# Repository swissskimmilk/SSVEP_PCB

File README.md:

# SSVEP EEG board

A 4-channel EEG board that streams over BLE, with a photodiode that marks screen flashes
in the same samples as the EEG.

```
host/      PyQt6 control + stimulus windows, recording, analysis
firmware/  XIAO nRF52840 firmware (PlatformIO)
SSVEP_PCB/ KiCad project
design/    circuit JSON, BOM, scripts
fab/       Gerbers
```

## Quick start

```
cd host && pip install -e . && python -m ssvep_host    # pick "Simulator" to try it
cd firmware && pio run -t upload                        # flash the board over USB
```

## Docs

- [Running a session](docs/session.md)
- [Hardware](docs/hardware.md)
- [Protocol](docs/protocol.md)
- [Bring-up](docs/bringup.md)

> Never put electrodes on a person while USB is plugged in. Battery and BLE only.

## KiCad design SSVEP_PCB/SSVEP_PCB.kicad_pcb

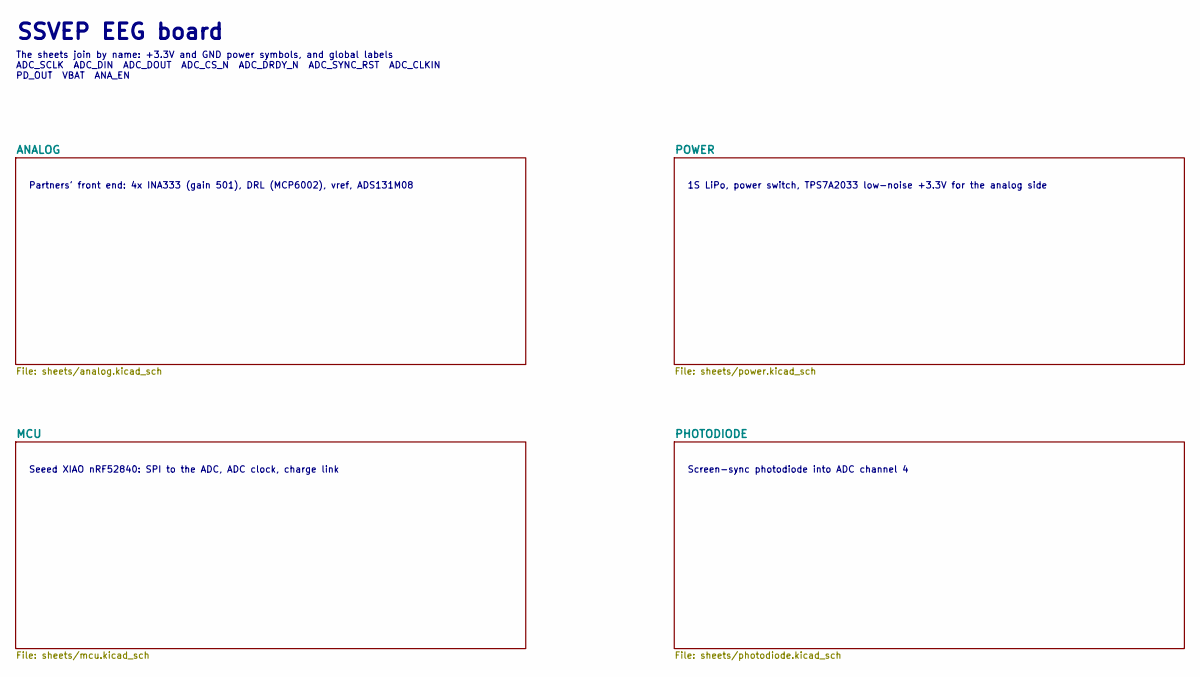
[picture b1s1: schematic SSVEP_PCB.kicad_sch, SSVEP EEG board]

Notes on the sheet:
SSVEP EEG board
The sheets join by name: +3.3V and GND power symbols, and global labels ADC_SCLK ADC_DIN ADC_DOUT ADC_CS_N ADC_DRDY_N ADC_SYNC_RST ADC_CLKIN PD_OUT VBAT ANA_EN
Partners' front end: 4x INA333 (gain 501), DRL (MCP6002), vref, ADS131M08
1S LiPo, power switch, TPS7A2033 low-noise +3.3V for the analog side
Seeed XIAO nRF52840: SPI to the ADC, ADC clock, charge link
Screen-sync photodiode into ADC channel 4

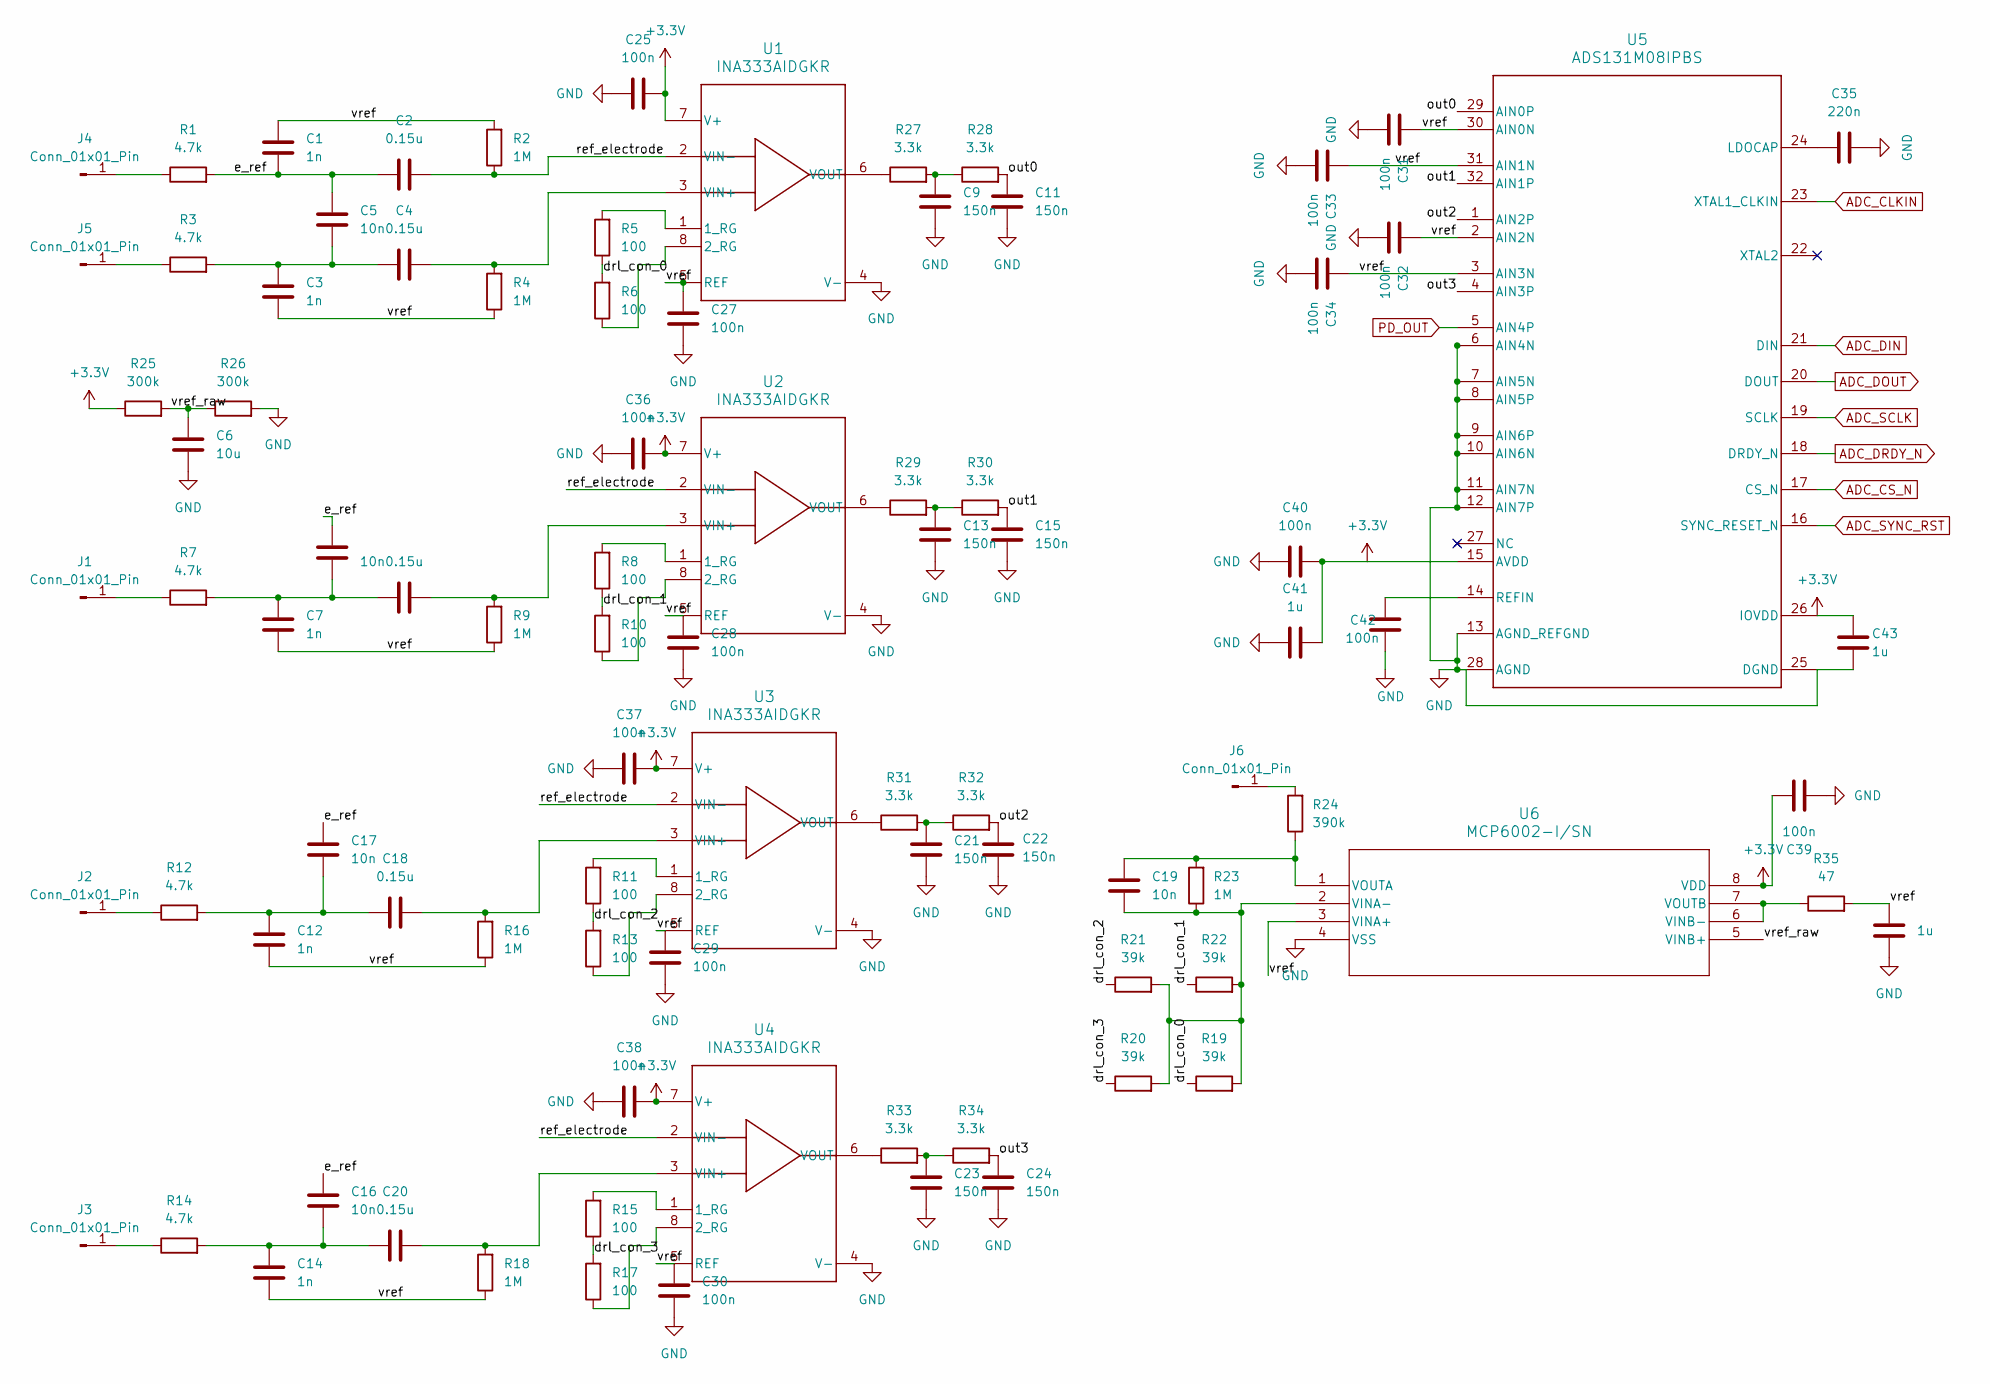
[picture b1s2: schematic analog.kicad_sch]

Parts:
C1, C3, C7, C12, C14: 1n; C_0805_2012Metric_Pad1.18x1.45mm_HandSolder; Voltage Rating 50V; MPN CL21C102JBC1PNC; DigiKey_PN 1276-2575-1-ND
C2, C4, C10, C18, C20: 0.15u; C_0805_2012Metric_Pad1.18x1.45mm_HandSolder; Voltage Rating 35V; MPN 35MF154KZ22012; DigiKey_PN 1189-35MF154KZ22012CT-ND
C5, C8, C16, C17, C19: 10n; C_0805_2012Metric_Pad1.18x1.45mm_HandSolder; Voltage Rating 50V; MPN CL21C103JBF1PNE; DigiKey_PN 1276-6790-1-ND
C6: 10u; C_0805_2012Metric_Pad1.18x1.45mm_HandSolder; Voltage Rating 25V; MPN C2012X5R1E106K125AB; DigiKey_PN 445-5984-1-ND
C9, C11, C13, C15, C21, C22, C23, C24: 150n; C_0805_2012Metric_Pad1.18x1.45mm_HandSolder; Voltage Rating 50V; MPN KGM21ER71H154KU; DigiKey_PN 478-KGM21ER71H154KUCT-ND
C25, C27, C28, C29, C30, C31, C32, C33, C34, C36, C37, C38, C39, C40, C42: 100n; C_0805_2012Metric_Pad1.18x1.45mm_HandSolder; Voltage Rating 50V; MPN CL21B104KBCNNNC; DigiKey_PN 1276-1003-1-ND
C26, C41, C43: 1u; C_0805_2012Metric_Pad1.18x1.45mm_HandSolder; Voltage Rating 25V; MPN CL21B105KAFNNNE; DigiKey_PN 1276-1066-1-ND
C35: 220n; C_0805_2012Metric_Pad1.18x1.45mm_HandSolder; Voltage Rating 50V; MPN CL21B224KBFVPNE; DigiKey_PN 1276-7012-1-ND
J1, J2, J3, J4, J5, J6: Conn_01x01_Pin; PinHeader_1x01_P2.54mm_Vertical; MPN TSW-101-07-G-S; DigiKey_PN 612-TSW-101-07-G-S-ND
R1, R3, R7, R12, R14: 4.7k; R_0805_2012Metric_Pad1.20x1.40mm_HandSolder; MPN RC0805FR-074K7L; DigiKey_PN 311-4.70KCRCT-ND
R2, R4, R9, R16, R18, R23: 1M; R_0805_2012Metric_Pad1.20x1.40mm_HandSolder; MPN RC0805FR-071ML; DigiKey_PN 311-1.00MCRCT-ND
R5, R6, R8, R10, R11, R13, R15, R17: 100; R_0805_2012Metric_Pad1.20x1.40mm_HandSolder; MPN RC0805FR-07100RL; DigiKey_PN 311-100CRCT-ND
R19, R20, R21, R22: 39k; R_0805_2012Metric_Pad1.20x1.40mm_HandSolder; MPN RC0805FR-0739KL; DigiKey_PN 311-39.0KCRCT-ND
R24: 390k; R_0805_2012Metric_Pad1.20x1.40mm_HandSolder; MPN RC0805FR-07390KL; DigiKey_PN 311-390KCRCT-ND
R25, R26: 300k; R_0805_2012Metric_Pad1.20x1.40mm_HandSolder; MPN RC0805FR-07300KL; DigiKey_PN 311-300KCRCT-ND
R27, R28, R29, R30, R31, R32, R33, R34: 3.3k; R_0805_2012Metric_Pad1.20x1.40mm_HandSolder; MPN RC0805FR-073K3L; DigiKey_PN 311-3.30KCRCT-ND
R35: 47; R_0805_2012Metric_Pad1.20x1.40mm_HandSolder; MPN RC0805FR-0747RL; DigiKey_PN 311-47.0CRCT-ND
U1, U2, U3, U4: INA333AIDGKR; DGK0008A-IPC_A
U5: ADS131M08IPBS; TQFP-32_5x5mm_P0.5mm
U6: MCP6002-I/SN; SOIC8-N_MC_MCH

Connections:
+3.3V: C25.1, C36.1, C37.1, C38.1, C39.1, C40.1, C41.1, C43.1, R25.1, U1.7 (V+), U2.7 (V+), U3.7 (V+), U4.7 (V+), U5.15 (AVDD), U5.26 (IOVDD), U6.8 (VDD); also elsewhere on the board
/ANALOG/drl_con_0: R5.1, R6.2, R19.1
/ANALOG/drl_con_1: R8.1, R10.2, R22.1
/ANALOG/drl_con_2: R11.1, R13.2, R21.1
/ANALOG/drl_con_3: R15.1, R17.2, R20.1
/ANALOG/e_ref: C1.2, C2.1, C5.1, C8.1, C16.1, C17.1, R1.2
/ANALOG/out0: C11.1, R28.2, U5.29 (AIN0P)
/ANALOG/out1: C15.1, R30.2, U5.32 (AIN1P)
/ANALOG/out2: C22.1, R32.2, U5.1 (AIN2P)
/ANALOG/out3: C24.1, R34.2, U5.4 (AIN3P)
/ANALOG/ref_electrode: C2.2, R2.1, U1.2 (VIN-), U2.2 (VIN-), U3.2 (VIN-), U4.2 (VIN-)
/ANALOG/vref: C1.1, C3.2, C7.2, C12.2, C14.2, C26.1, C27.1, C28.1, C29.1, C30.1, C31.1, C32.1, C33.1, C34.1, R2.2, R4.1, R9.1, R16.1, R18.1, R35.2, U1.5 (REF), U2.5 (REF), U3.5 (REF), U4.5 (REF), U5.2 (AIN2N), U5.3 (AIN3N), U5.30 (AIN0N), U5.31 (AIN1N), U6.3 (VINA+)
/ANALOG/vref_raw: C6.1, R25.2, R26.1, U6.5 (VINB+)
ADC_CLKIN: U5.23 (XTAL1_CLKIN); also elsewhere on the board
ADC_CS_N: U5.17 (CS_N); also elsewhere on the board
ADC_DIN: U5.21 (DIN); also elsewhere on the board
ADC_DOUT: U5.20 (DOUT); also elsewhere on the board
ADC_DRDY_N: U5.18 (DRDY_N); also elsewhere on the board
ADC_SCLK: U5.19 (SCLK); also elsewhere on the board
ADC_SYNC_RST: U5.16 (SYNC_RESET_N); also elsewhere on the board
unnamed: C3.1, C4.1, C5.2, R3.2
unnamed: C9.1, R27.2, R28.1
unnamed: C7.1, C8.2, C10.1, R7.2
unnamed: C12.1, C17.2, C18.1, R12.2
unnamed: C13.1, R29.2, R30.1
unnamed: C14.1, C16.2, C20.1, R14.2
unnamed: C21.1, R31.2, R32.1
unnamed: C23.1, R33.2, R34.1
unnamed: J1.1 (Pin_1_1), R7.1
unnamed: J2.1 (Pin_1_1), R12.1
unnamed: J3.1 (Pin_1_1), R14.1
unnamed: J4.1 (Pin_1_1), R1.1
unnamed: J5.1 (Pin_1_1), R3.1
unnamed: J6.1 (Pin_1_1), R24.2
unnamed: R5.2, U1.1 (1_RG)
unnamed: R6.1, U1.8 (2_RG)
unnamed: C4.2, R4.2, U1.3 (VIN+)
unnamed: R27.1, U1.6 (VOUT)
unnamed: R8.2, U2.1 (1_RG)
unnamed: R10.1, U2.8 (2_RG)
unnamed: C10.2, R9.2, U2.3 (VIN+)
unnamed: R29.1, U2.6 (VOUT)
unnamed: R11.2, U3.1 (1_RG)
unnamed: R13.1, U3.8 (2_RG)
unnamed: C18.2, R16.2, U3.3 (VIN+)
unnamed: R31.1, U3.6 (VOUT)
unnamed: R15.2, U4.1 (1_RG)
unnamed: R17.1, U4.8 (2_RG)
unnamed: C20.2, R18.2, U4.3 (VIN+)
unnamed: R33.1, U4.6 (VOUT)
unnamed: C35.1, U5.24 (LDOCAP)
unnamed: C42.1, U5.14 (REFIN)
unnamed: C19.2, R19.2, R20.2, R21.2, R22.2, R23.1, U6.2 (VINA-)
unnamed: R35.1, U6.6 (VINB-), U6.7 (VOUTB)
unnamed: C19.1, R23.2, R24.1, U6.1 (VOUTA)
PD_OUT: U5.5 (AIN4P); also elsewhere on the board

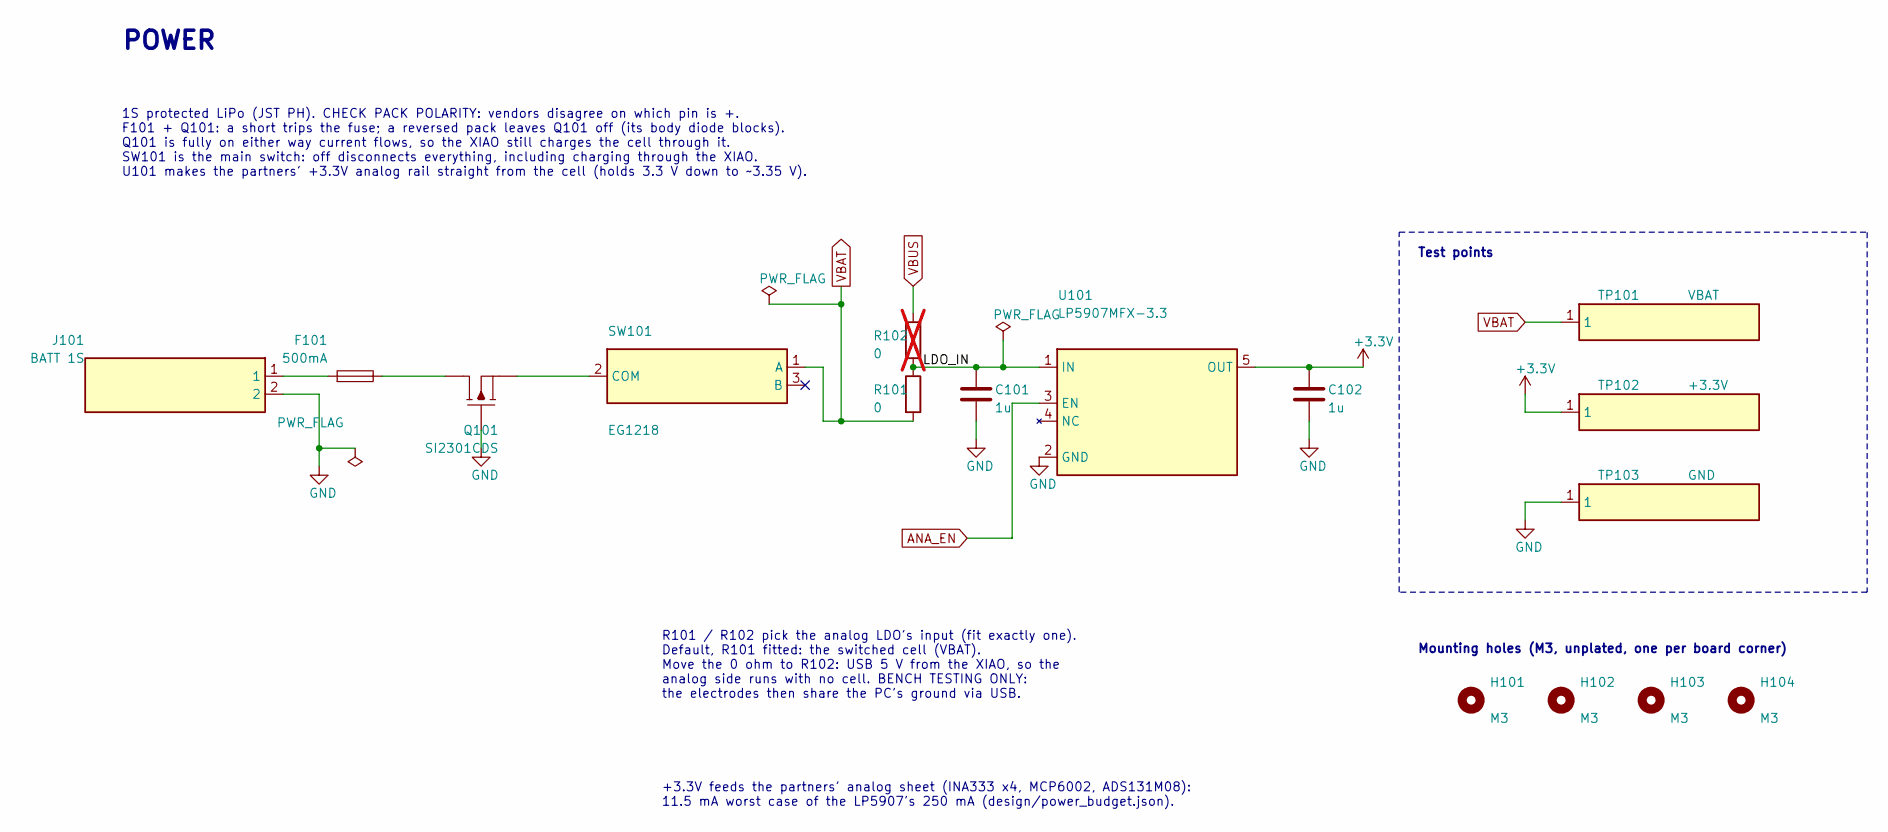
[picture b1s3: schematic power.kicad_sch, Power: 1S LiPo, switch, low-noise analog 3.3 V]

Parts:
C101, C102: 1u; C_0805_2012Metric_Pad1.18x1.45mm_HandSolder; MPN CL21B105KAFNNNE; DigiKey_PN 1276-1066-1-ND
F101: 500mA; Fuse_1206_3216Metric; MPN 0466.500NR; DigiKey_PN F1454CT-ND
H101, H102, H103, H104: M3; MountingHole_3.2mm_M3
J101: BATT 1S; JST_PH_B2B-PH-K_1x02_P2.00mm_Vertical; MPN B2B-PH-K-S
Q101: SI2301CDS; SOT-23; MPN SI2301CDS-T1-BE3; DigiKey_PN 742-SI2301CDS-T1-BE3CT-ND
R101: 0; R_0805_2012Metric_Pad1.20x1.40mm_HandSolder; MPN RC0805JR-070RL
R102: 0; R_0805_2012Metric_Pad1.20x1.40mm_HandSolder; MPN RC0805JR-070RL; not fitted
SW101: EG1218; SW_Slide_SPDT_EG1218; MPN EG1218
TP101: VBAT; TestPoint_Keystone_5015_Micro_Mini; MPN 5015
TP102: +3.3V; TestPoint_Keystone_5015_Micro_Mini; MPN 5015
TP103: GND; TestPoint_Keystone_5015_Micro_Mini; MPN 5015
U101: LP5907MFX-3.3; SOT-23-5; MPN LP5907MFX-3.3/NOPB; DigiKey_PN 296-38557-1-ND

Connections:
+3.3V: C102.1, TP102.1, U101.5 (OUT); also elsewhere on the board
ANA_EN: U101.3 (EN); also elsewhere on the board
unnamed: F101.1, J101.1
unnamed: F101.2, Q101.3 (D)
unnamed: Q101.2 (S), SW101.2 (COM)
VBUS: R102.1; also elsewhere on the board

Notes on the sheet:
POWER
1S protected LiPo (JST PH). CHECK PACK POLARITY: vendors disagree on which pin is +. F101 + Q101: a short trips the fuse; a reversed pack leaves Q101 off (its body diode blocks). Q101 is fully on either way current flows, so the XIAO still charges the cell through it. SW101 is the main switch: off 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
R101 / R102 pick the analog LDO's input (fit exactly one). Default, R101 fitted: the switched cell (VBAT). Move the 0 ohm to R102: USB 5 V from the XIAO, so the analog side runs with no cell. BENCH TESTING ONLY: the electrodes then share the PC's ground via USB.
Test points
Mounting holes (M3, unplated, one per board corner)
+3.3V feeds the partners' analog sheet (INA333 x4, MCP6002, ADS131M08): 11.5 mA worst case of the LP5907's 250 mA (design/power_budget.json).

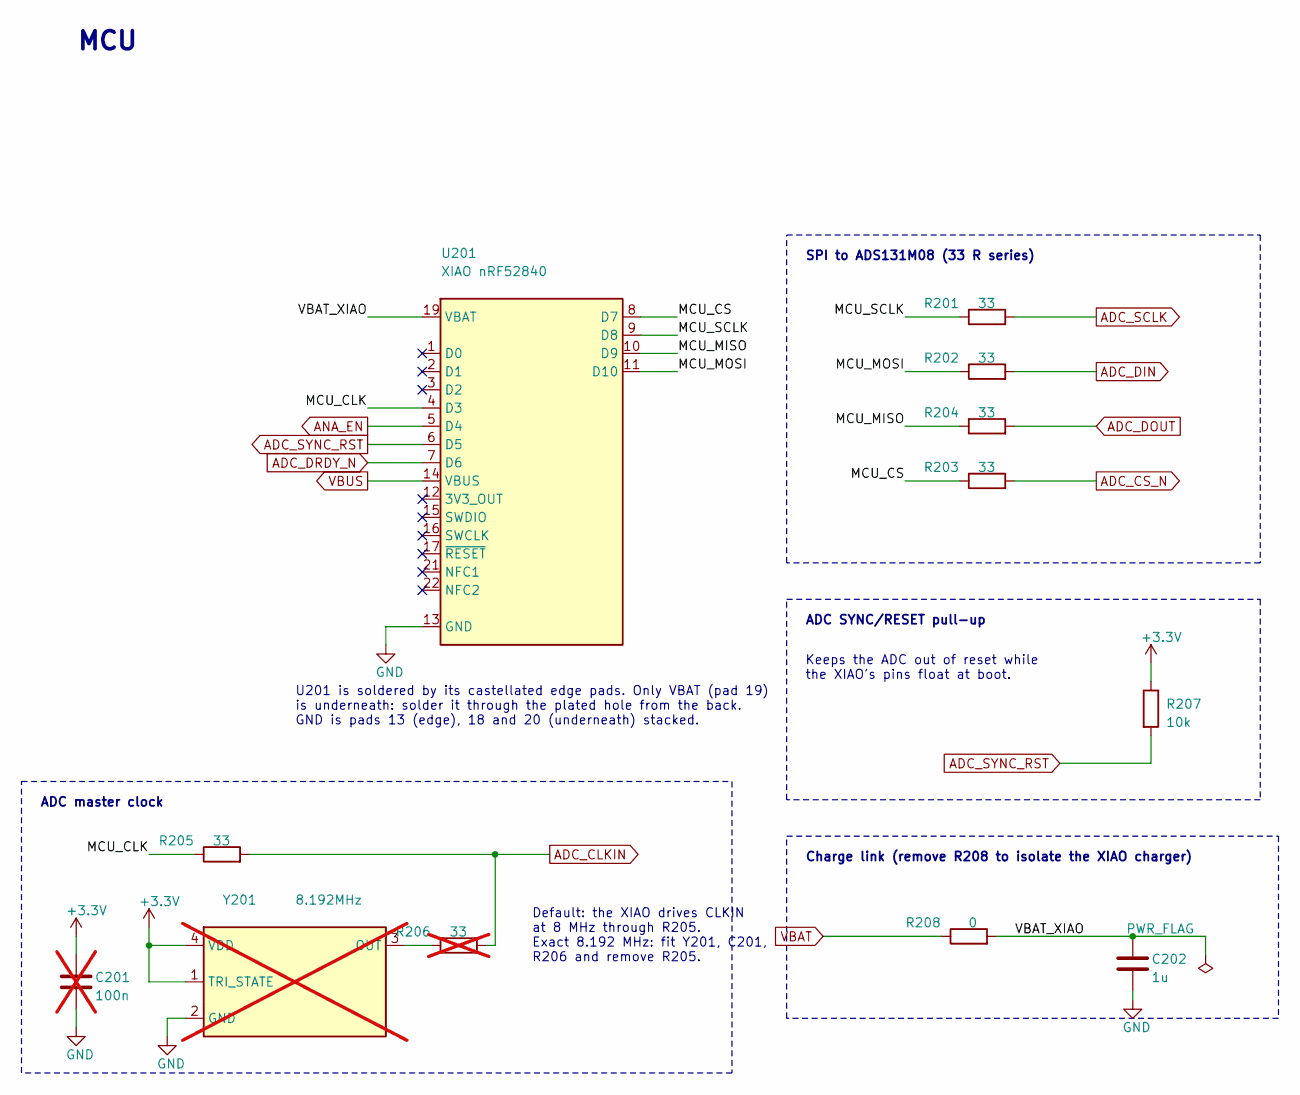
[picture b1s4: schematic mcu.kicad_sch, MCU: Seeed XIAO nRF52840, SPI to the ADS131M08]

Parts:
C201: 100n; C_0805_2012Metric_Pad1.18x1.45mm_HandSolder; MPN CL21B104KBCNNNC; not fitted
C202: 1u; C_0805_2012Metric_Pad1.18x1.45mm_HandSolder; MPN CL21B105KAFNNNE; DigiKey_PN 1276-1066-1-ND
R201, R202, R203, R204, R205: 33; R_0805_2012Metric_Pad1.20x1.40mm_HandSolder; MPN RC0805FR-0733RL
R206: 33; R_0805_2012Metric_Pad1.20x1.40mm_HandSolder; MPN RC0805FR-0733RL; not fitted
R207: 10k; R_0805_2012Metric_Pad1.20x1.40mm_HandSolder; MPN RC0805FR-0710KL
R208: 0; R_0805_2012Metric_Pad1.20x1.40mm_HandSolder; MPN RC0805JR-070RL
U201: XIAO nRF52840; XIAO-nRF52840-SMD_VBAT-hole; MPN 102010448
Y201: 8.192MHz; Oscillator_SMD_ECS_2520MV-xxx-xx-4Pin_2.5x2.0mm; MPN ECS-2520MVLC-081.92-CN-TR; not fitted

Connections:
+3.3V: C201.1, R207.1, Y201.1 (TRI_STATE), Y201.4 (VDD); also elsewhere on the board
/MCU/MCU_CLK: R205.1, U201.4 (D3)
/MCU/MCU_CS: R203.1, U201.8 (D7)
/MCU/MCU_MISO: R204.1, U201.10 (D9)
/MCU/MCU_MOSI: R202.1, U201.11 (D10)
/MCU/MCU_SCLK: R201.1, U201.9 (D8)
/MCU/VBAT_XIAO: C202.1, R208.2, U201.19 (VBAT)
ADC_CLKIN: R205.2, R206.2; also elsewhere on the board
ADC_CS_N: R203.2; also elsewhere on the board
ADC_DIN: R202.2; also elsewhere on the board
ADC_DOUT: R204.2; also elsewhere on the board
ADC_DRDY_N: U201.7 (D6); also elsewhere on the board
ADC_SCLK: R201.2; also elsewhere on the board
ADC_SYNC_RST: R207.2, U201.6 (D5); also elsewhere on the board
ANA_EN: U201.5 (D4); also elsewhere on the board
unnamed: R206.1, Y201.3 (OUT)
VBUS: U201.14 (VBUS); also elsewhere on the board

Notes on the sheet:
MCU
U201 is soldered by its castellated edge pads. Only VBAT (pad 19) is underneath: solder it through the plated hole from the back. GND is pads 13 (edge), 18 and 20 (underneath) stacked.
SPI to ADS131M08 (33 R series)
ADC master clock
Default: the XIAO drives CLKIN at 8 MHz through R205. Exact 8.192 MHz: fit Y201, C201, R206 and remove R205.
ADC SYNC/RESET pull-up
Keeps the ADC out of reset while the XIAO's pins float at boot.
Charge link (remove R208 to isolate the XIAO charger)

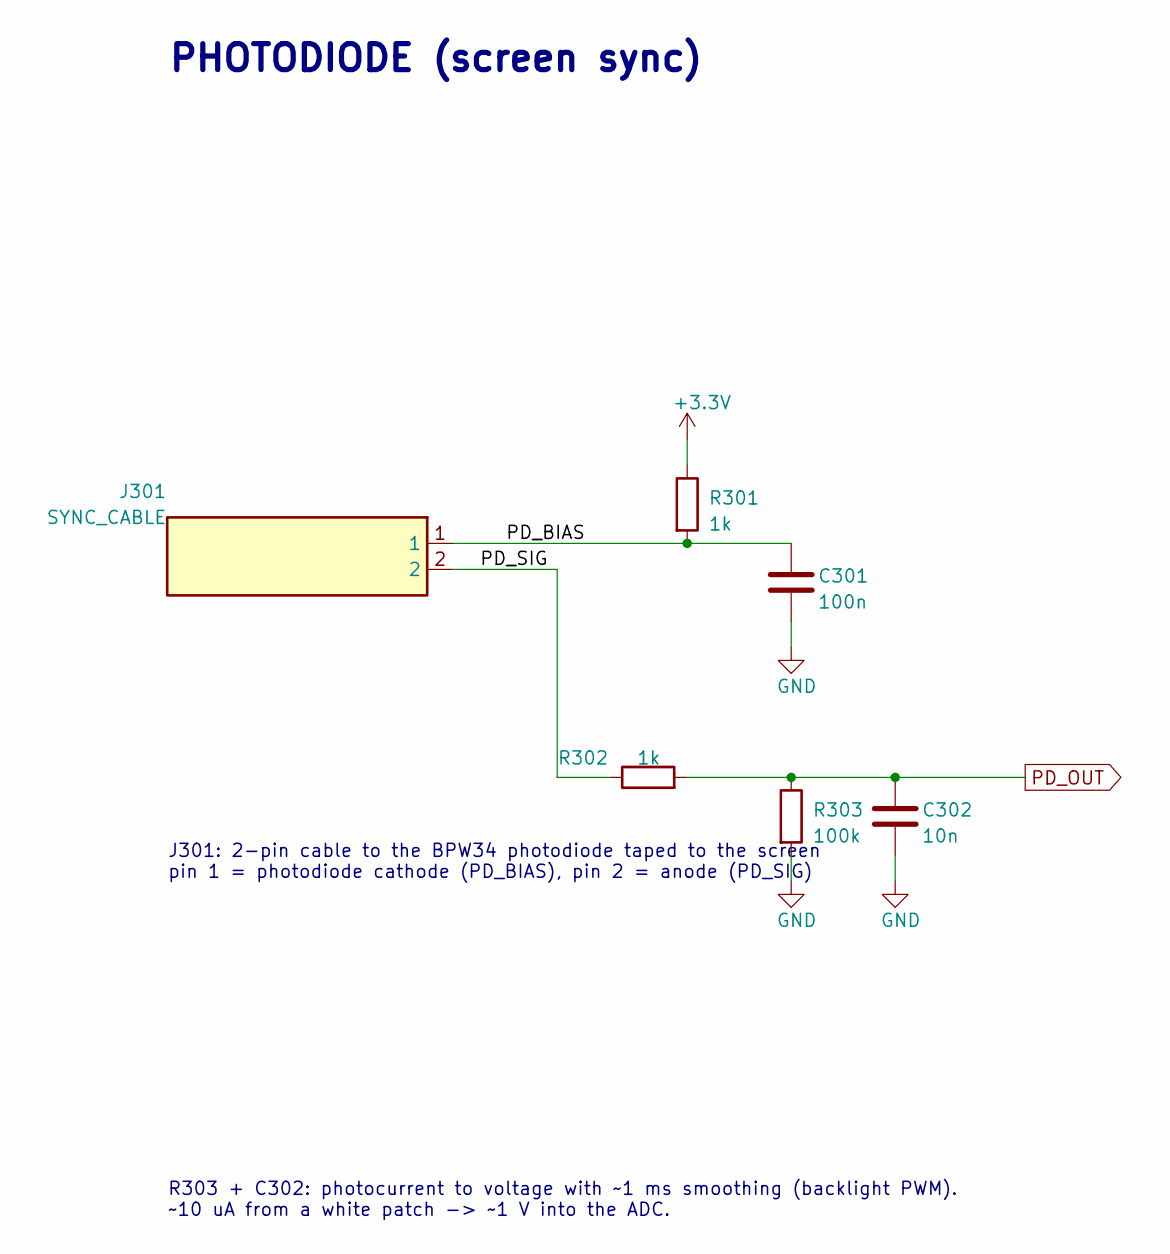
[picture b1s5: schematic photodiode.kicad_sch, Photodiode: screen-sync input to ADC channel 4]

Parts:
C301: 100n; C_0805_2012Metric_Pad1.18x1.45mm_HandSolder; MPN CL21B104KBCNNNC
C302: 10n; C_0805_2012Metric_Pad1.18x1.45mm_HandSolder; MPN CL21C103JBF1PNE
J301: SYNC_CABLE; JST_PH_B2B-PH-K_1x02_P2.00mm_Vertical; MPN B2B-PH-K-S
R301, R302: 1k; R_0805_2012Metric_Pad1.20x1.40mm_HandSolder; MPN RC0805FR-071KL
R303: 100k; R_0805_2012Metric_Pad1.20x1.40mm_HandSolder; MPN RC0805FR-07100KL

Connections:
+3.3V: R301.1; also elsewhere on the board
/PHOTODIODE/PD_BIAS: C301.1, J301.1, R301.2
/PHOTODIODE/PD_SIG: J301.2, R302.1
PD_OUT: C302.1, R302.2, R303.1; also elsewhere on the board

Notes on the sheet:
PHOTODIODE (screen sync)
J301: 2-pin cable to the BPW34 photodiode taped to the screen pin 1 = photodiode cathode (PD_BIAS), pin 2 = anode (PD_SIG)
R303 + C302: photocurrent to voltage with ~1 ms smoothing (backlight PWM). ~10 uA from a white patch -> ~1 V into the ADC.

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
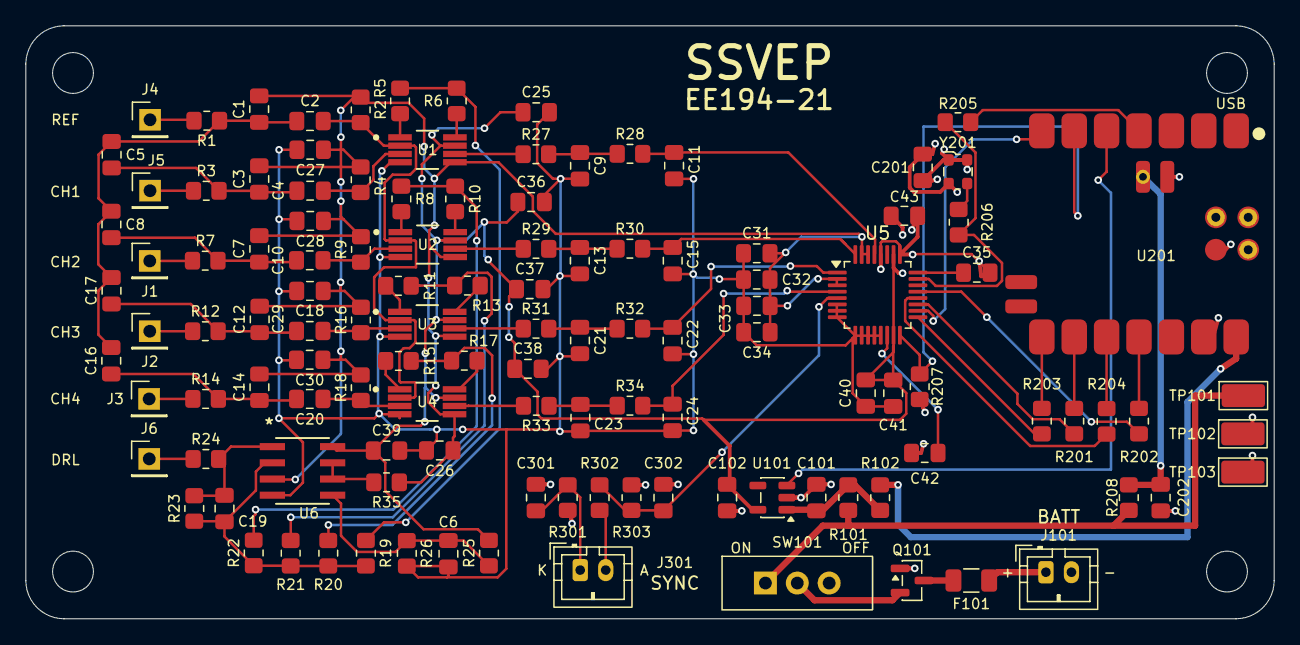
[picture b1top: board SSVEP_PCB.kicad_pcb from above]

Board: 4 copper layers, 97.9 x 46.5 mm, 124 parts (0 on the bottom side), 73 nets.

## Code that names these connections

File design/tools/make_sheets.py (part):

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    s.wire(qs, com)
    s.nc(b)

    # VBAT row (switch -> VBAT global label + PWR_FLAG -> R101); R101 or R102 -> LDO_IN -> C101 -> U101.IN
    s.place("U101", "SSVEP:LP5907MFX-3.3", 170.18, 81.28, value="LP5907MFX-3.3",
            footprint="Package_TO_SOT_SMD:SOT-23-5", datasheet="https://www.ti.com/lit/gpn/lp5907",
            mpn="LP5907MFX-3.3/NOPB", fields={"Manufacturer": "Texas Instruments", "DigiKey_PN": "296-38557-1-ND"}, ref_at=(157.48, 64.77), val_at=(157.48, 67.31))
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    cx, fx = 146.05, 149.86
    s.wire((jx, yv), (cx, yv), (fx, yv), vin)
    s.junction((jx, yv)); s.junction((cx, yv)); s.junction((fx, yv))
    s.label("LDO_IN", (jx + 1.27, yv))
    # fed through a link (passive), so tell ERC this net is supplied
    s.wire((fx, yv), (fx, yv - 3.81))
    s.power("power:PWR_FLAG", (fx, yv - 3.81))
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    # pin 4 is typed no_connect in the generated symbol: no flag needed
    s.power(GND, gnd)
    s.wire(en, (151.13, en[1]), (151.13, 99.06), (144.78, 99.06))
    s.glabel("ANA_EN", (144.78, 99.06), angle=180, shape="input")
    s.text("R101 / R102 pick the analog LDO's input (fit exactly one).\n"
           "Default, R101 fitted: the switched cell (VBAT).\n"
           "Move the 0 ohm to R102: USB 5 V from the XIAO, so the\n"
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    s = sheet("mcu", "MCU: Seeed XIAO nRF52840, SPI to the ADS131M08", "3",
              ("D8 SCLK, D10 MOSI, D9 MISO, D7 CS, D6 DRDY",
               "D5 SYNC/RST, D4 ANA_EN, D3 CLKIN; D0-D2 spare",
               "FW: ADC pins low/high-Z before ANA_EN goes low"))
    s.text("MCU", (25.4, 30.48), size=2.54, bold=True)

    X, Y = 88.9, 88.9
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    for n in ("1", "2", "3", "12", "15", "16", "17", "21", "22"):
        s.nc(p(n))
    lx = 66.04                                    # left stub ends
    v = p("19"); s.wire(v, (lx, v[1])); s.label("VBAT_XIAO", (lx, v[1]), angle=180)
    u = p("14"); s.wire(u, (lx, u[1])); s.glabel("VBUS", (lx, u[1]), angle=180, shape="output")
    for n, kind, name, shape in (("4", "l", "MCU_CLK", None), ("5", "g", "ANA_EN", "output"),
                                 ("6", "g", "ADC_SYNC_RST", "output"), ("7", "g", "ADC_DRDY_N", "input")):
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    y = 142.24
    l, r = res_h(s, "R205", "33", 45.72, y)
    s.wire((35.56, y), l)
    s.label("MCU_CLK", (35.56, y), angle=180)
    node = (83.82, y)
    s.wire(r, node, (91.44, y))
    s.junction(node)
    s.glabel("ADC_CLKIN", (91.44, y), shape="output")
    s.place("Y201", "SSVEP:ECS-2520MVLC-081.92-CN-TR", 55.88, 160.02, value="8.192MHz",
            footprint="Oscillator:Oscillator_SMD_ECS_2520MV-xxx-xx-4Pin_2.5x2.0mm",
            datasheet="https://ecsxtal.com/store/pdf/ECS-2520MVLC.pdf", mpn="ECS-2520MVLC-081.92-CN-TR",
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    top, bot = res_v(s, "R207", "10k", 175.26, 121.92)
    p33_above(s, top)
    s.wire(bot, (175.26, 129.54), (162.56, 129.54))
    s.glabel("ADC_SYNC_RST", (162.56, 129.54), angle=180, shape="input")
    s.text("Keeps the ADC out of reset while\nthe XIAO's pins float at boot.", (127.0, 118.11))

    # ---- charge link and XIAO VBAT decoupling
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    cx = 172.72
    s.wire(jb, (cx, y), (182.88, y))
    s.junction((cx, y))
    s.label("VBAT_XIAO", (jb[0] + 2.54, y))
    # fed through the link (passive), so tell ERC this net is supplied
    s.wire((182.88, y), (182.88, 156.21))
    s.power("power:PWR_FLAG", (182.88, 156.21), rot=180)
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            ref_at=(25.4, 71.12), val_at=(25.4, 73.66))
    k, a = s.pin("J301", "1"), s.pin("J301", "2")                    # (53.34, 76.2), (53.34, 78.74)
    s.text("J301: 2-pin cable to the BPW34 photodiode taped to the screen\n"
           "pin 1 = photodiode cathode (PD_BIAS), pin 2 = anode (PD_SIG)", (25.4, 109.22))
    bx, cx = 76.2, 86.36
    s.wire(k, (bx, k[1]), (cx, k[1]))
    s.junction((bx, k[1]))
    s.label("PD_BIAS", (58.42, k[1]))
    top, bot = res_v(s, "R301", "1k", bx, k[1] - 3.81)
    p33_above(s, top)
    c_top, c_bot = cap_v(s, "C301", "100n", "CL21B104KBCNNNC", cx, k[1] + 3.81)
    gnd_below(s, c_bot)
    y = 99.06
    s.wire(a, (63.5, a[1]), (63.5, y))
    s.label("PD_SIG", (55.88, a[1]))
    l, r = res_h(s, "R302", "1k", 72.39, y)
    s.wire((63.5, y), l)
    x3, x4, xo = 86.36, 96.52, 109.22
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    gnd_below(s, b3)
    t4, b4 = cap_v(s, "C302", "10n", "CL21C103JBF1PNE", x4, y + 3.81)
    gnd_below(s, b4)
    s.glabel("PD_OUT", (xo, y), shape="output")
    s.text("R303 + C302: photocurrent to voltage with ~1 ms smoothing (backlight PWM).\n"
           "~10 uA from a white patch -> ~1 V into the ADC.", (25.4, 142.24))
    s.write(OUT / "photodiode.kicad_sch")
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
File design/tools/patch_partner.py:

"""patch_partner.py -- the minimal, additive edits to the partners' root sheet.

SUPERSEDED: already applied, then restructure.py moved that page to sheets/analog.kicad_sch under a
sheet-boxes-only root. Kept as the record of exactly what was edited on the partners' page.

    python patch_partner.py

Text-level patch so every line we do not touch stays byte-identical. Backs the original up to
design/backup/ the first time. Edits:
  * ADS131M08 (U5) digital pins -> global labels (ADC_SCLK, ADC_DIN, ADC_DOUT, ADC_CS_N,
    ADC_DRDY_N, ADC_SYNC_RST, ADC_CLKIN); XTAL2 no-connect (external clock)
  * AVDD pin 27 wired to the +3.3V already on pin 15
  * REFIN -> C42 100 nF to GND (datasheet's internal-reference test condition)
  * AIN4P lifted off the unused-input ground strap -> global label PD_OUT (photodiode)
  * three sheet boxes for sheets/power, sheets/mcu, sheets/photodiode
NOT touched: C28-C30 (pin 1 floating) -- that is the partners' call.
"""
import shutil
import sys
from pathlib import Path

import ksch
from ksch import f, q, uid
from make_sheets import ROOT_UUID, SHEET_UUID, C_FP

SCH = Path("C:/Users/aidan/SSVEP_PCB/SSVEP_PCB/SSVEP_PCB.kicad_sch")
BACKUP = Path("C:/Users/aidan/SSVEP_PCB/design/backup/SSVEP_PCB.kicad_sch.orig")
PROJECT = "SSVEP_PCB"


def remove_block(lines, head, needle):
    """Delete the top-level `\\t(head` block whose text contains `needle`."""
    for i, line in enumerate(lines):
        if line.rstrip("\n") == f"\t({head}":
            j = i
            while lines[j].rstrip("\n") != "\t)":
                j += 1
            if any(needle in lines[k] for k in range(i, j + 1)):
                del lines[i:j + 1]
                return
    raise SystemExit(f"not found: {head} containing {needle!r} -- has the partners' sheet changed?")


def wire(a, b):
    return ["wire", ["pts", ["xy", f(a[0]), f(a[1])], ["xy", f(b[0]), f(b[1])]],
            ["stroke", ["width", "0"], ["type", "default"]], ["uuid", q(uid())]]


def glabel(name, p, angle, shape):
    just = "left" if angle == 0 else "right"
    return ["global_label", q(name), ["shape", shape], ["at", f(p[0]), f(p[1]), str(angle)],
            ["fields_autoplaced", "yes"], ["effects", ["font", ["size", "1.27", "1.27"]], ["justify", just]],
            ["uuid", q(uid())],
            ["property", q("Intersheetrefs"), q("${INTERSHEET_REFS}"), ["at", f(p[0]), f(p[1]), "0"],
             ["effects", ["font", ["size", "1.27", "1.27"]], ["justify", just], ["hide", "yes"]]]]


def symbol(lib_id, ref, value, x, y, footprint="", datasheet="", mpn="", ref_at=None, val_at=None,
           hide_ref=False, pins=("1", "2"), power=False):
    eff = lambda just=None, hide=False: (["effects", ["font", ["size", "1.27", "1.27"]]]
                                         + ([["justify", just]] if just else []) + ([["hide", "yes"]] if hide else []))
    rx, ry = ref_at or (x, y)
    vx, vy = val_at or (x, y)
    node = ["symbol", ["lib_id", q(lib_id)], ["at", f(x), f(y), "0"], ["unit", "1"],
            ["exclude_from_sim", "no"], ["in_bom", "no" if power else "yes"],
            ["on_board", "no" if power else "yes"], ["dnp", "no"], ["fields_autoplaced", "no"],
            ["uuid", q(uid())],
            ["property", q("Reference"), q(ref), ["at", f(rx), f(ry), "0"], eff("left", hide_ref)],
            ["property", q("Value"), q(value), ["at", f(vx), f(vy), "0"], eff("left")],
            ["property", q("Footprint"), q(footprint), ["at", f(x), f(y), "0"], eff(hide=True)],
            ["property", q("Datasheet"), q(datasheet), ["at", f(x), f(y), "0"], eff(hide=True)]]
    if mpn:
        node.append(["property", q("MPN"), q(mpn), ["at", f(x), f(y), "0"], eff(hide=True)])
    node += [["pin", q(n), ["uuid", q(uid())]] for n in pins]
    node.append(["instances", ["project", q(PROJECT), ["path", q("/" + ROOT_UUID), ["reference", q(ref)], ["unit", "1"]]]])
    return node


def sheet_box(name, file, x, y, page):
    w, h = 16.51, 10.16
    return ["sheet", ["at", f(x), f(y)], ["size", f(w), f(h)], ["exclude_from_sim", "no"],
            ["in_bom", "yes"], ["on_board", "yes"], ["dnp", "no"], ["fields_autoplaced", "yes"],
            ["stroke", ["width", "0.1524"], ["type", "solid"]], ["fill", ["color", "0", "0", "0", "0.0000"]],
            ["uuid", q(SHEET_UUID[file])],
            ["property", q("Sheetname"), q(name), ["at", f(x), f(y - 0.7116), "0"],
             ["effects", ["font", ["size", "1.27", "1.27"]], ["justify", "left", "bottom"]]],
            ["property", q("Sheetfile"), q(f"sheets/{file}.kicad_sch"), ["at", f(x), f(y + h + 0.5846), "0"],
             ["effects", ["font", ["size", "1.27", "1.27"]], ["justify", "left", "top"], ["hide", "yes"]]],
            ["instances", ["project", q(PROJECT), ["path", q("/" + ROOT_UUID), ["page", q(page)]]]]]


def main():
    text = SCH.read_bytes().decode("utf-8")
    if "sheets/mcu.kicad_sch" in text:
        sys.exit("already patched")
    BACKUP.parent.mkdir(parents=True, exist_ok=True)
    if not BACKUP.exists():
        shutil.copy2(SCH, BACKUP)
    lines = text.splitlines(keepends=True)

    # AIN4P off the ground strap: the dangling stub above it, the segment down to AIN4N, its junction
    remove_block(lines, "wire", "(xy 213.36 53.34) (xy 213.36 54.61)")
    remove_block(lines, "wire", "(xy 213.36 54.61) (xy 213.36 57.15)")
    remove_block(lines, "junction", "(at 213.36 54.61)")

    new = []
    # U5 right side: digital pins out to global labels (shape is from the ADC's point of view)
    for name, y, shape in (("ADC_CLKIN", 36.83, "input"), ("ADC_DIN", 57.15, "input"),
                           ("ADC_DOUT", 62.23, "output"), ("ADC_SCLK", 67.31, "input"),
                           ("ADC_DRDY_N", 72.39, "output"), ("ADC_CS_N", 77.47, "input"),
                           ("ADC_SYNC_RST", 82.55, "input")):
        new += [wire((264.16, y), (266.7, y)), glabel(name, (266.7, y), 0, shape)]
    new.append(["no_connect", ["at", "264.16", "44.45"], ["uuid", q(uid())]])          # XTAL2
    # AVDD pin 27 -> the +3.3V on pin 15 (junction at 213.36 87.63 already exists)
    new.append(wire((213.36, 85.09), (213.36, 87.63)))
    # REFIN -> C42 -> GND (the wire crosses the ground strap at x 209.55 without touching it)
    new.append(wire((213.36, 92.71), (203.2, 92.71)))
    new.append(symbol("Device:C", "C42", "100n", 203.2, 96.52, footprint=C_FP,
                      datasheet="https://product.samsungsem.com/mlcc/CL21B104KBCNNN.do", mpn="CL21B104KBCNNNC",
                      ref_at=(198.12, 95.885), val_at=(197.485, 98.425)))
    new.append(wire((203.2, 100.33), (203.2, 102.87)))
    new.append(symbol("power:GND", "#PWR0901", "GND", 203.2, 102.87, ref_at=(203.2, 109.22),
                      val_at=(201.93, 106.68), hide_ref=True, pins=("1",), power=True))
    # AIN4P -> photodiode
    new.append(wire((213.36, 54.61), (210.82, 54.61)))
    new.append(glabel("PD_OUT", (210.82, 54.61), 180, "input"))
    # our sheets
    new += [sheet_box("POWER", "power", 147.32, 57.15, "2"),
            sheet_box("MCU", "mcu", 166.37, 57.15, "3"),
            sheet_box("PHOTODIODE", "photodiode", 185.42, 57.15, "4")]

    at = next(i for i, l in enumerate(lines) if l.rstrip("\n") == "\t(sheet_instances")
    block = "".join("\t" + ksch.dump(n, 1) + "\n" for n in new)
    lines.insert(at, block)
    SCH.write_bytes("".join(lines).encode("utf-8"))
    print(f"patched {SCH.name}: removed 2 wires + 1 junction, added {len(new)} items; backup {BACKUP}")


if __name__ == "__main__":
    main()
